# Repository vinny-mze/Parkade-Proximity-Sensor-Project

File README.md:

# microHat Project

Proximity sensor: License and README File

This HAT is a proximity sensor used in Parkade Parking and Home garages
It is used to aid in parking by switching on LED lights if a car gets too close to the wall.

How to use it
Attach sensor to wall
Ensure that all LED lights are in full view of driver's rear mirror
Plug in to 3V-75V DC Source
Keep away from direct sunlight

If car is within 4m from the sensor, 1 LED will switch on this means proceed
If car is within 1.5m from the sensor, 2 LEDs will switch on this means proceed with more caution
if car is less than 0.5m from the wall, all LEDs will switch on this means STOP 

Calvin Induna & Vincent Muzerengwa

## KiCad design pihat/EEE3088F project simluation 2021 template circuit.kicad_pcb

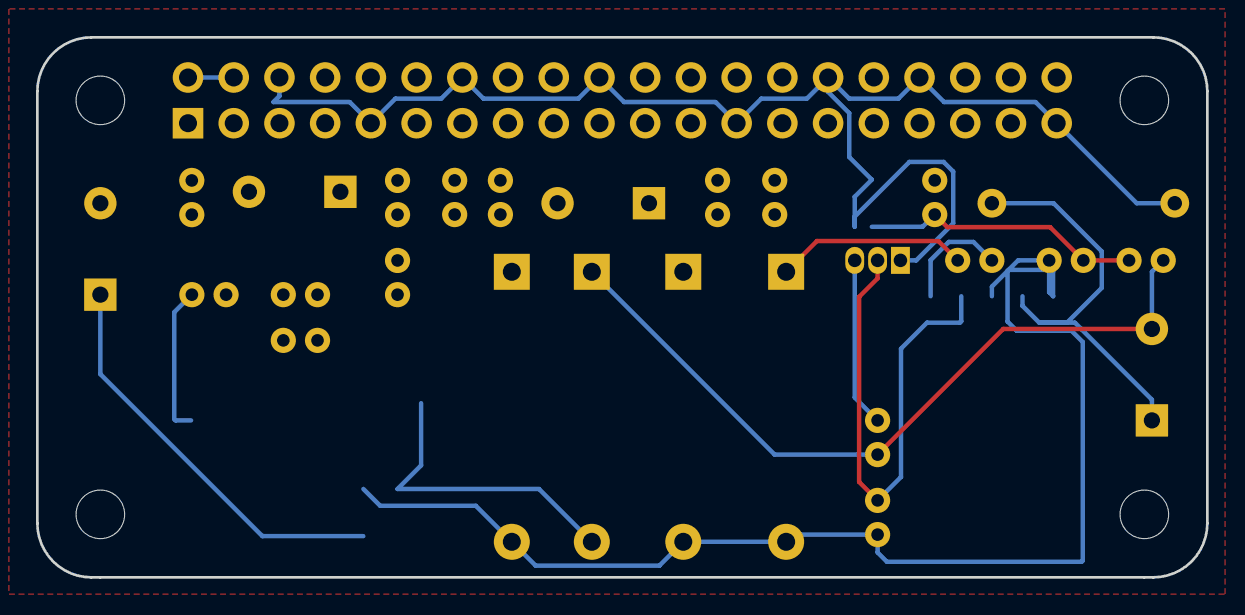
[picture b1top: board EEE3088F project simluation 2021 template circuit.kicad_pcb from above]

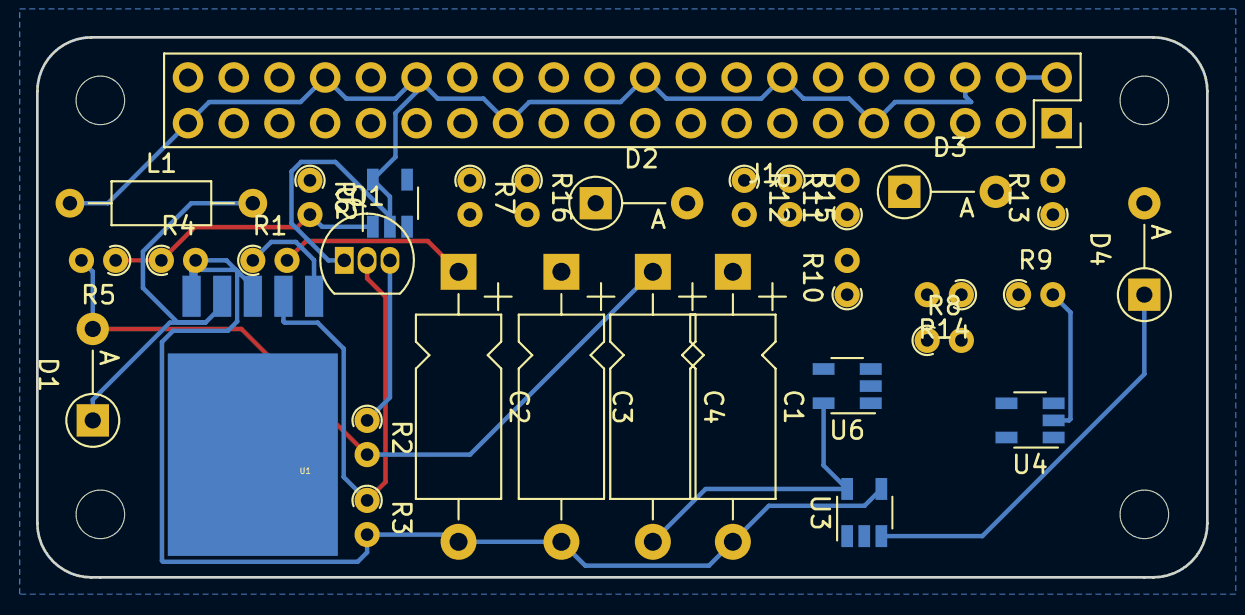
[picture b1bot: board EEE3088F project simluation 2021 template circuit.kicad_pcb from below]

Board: 2 copper layers, 65.0 x 30.0 mm, 36 parts (32 on the bottom side), 24 nets.

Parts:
C1: 33µ; CP_Axial_L10.0mm_D4.5mm_P15.00mm_Horizontal
C2: 0.22µ; CP_Axial_L10.0mm_D4.5mm_P15.00mm_Horizontal
C3: 0.01µ; CP_Axial_L10.0mm_D4.5mm_P15.00mm_Horizontal
C4: 470µ; CP_Axial_L10.0mm_D4.5mm_P15.00mm_Horizontal
D1, D2, D3, D4: D; D_A-405_P5.08mm_Vertical_AnodeUp
H1, H2, H3, H4: MountingHole; MountingHole_2.7mm_M2.5_uHAT_RPi
J1: GPIO_CONNECTOR; PinSocket_2x20_P2.54mm_Vertical_Centered_Anchor
L1: 250µ; L_Axial_L5.3mm_D2.2mm_P10.16mm_Horizontal_Vishay_IM-1
Q1: PNP; TO-92_Inline
R1: 4.7k; R_Axial_DIN0204_L3.6mm_D1.6mm_P1.90mm_Vertical
R2: 2k; R_Axial_DIN0204_L3.6mm_D1.6mm_P1.90mm_Vertical
R3: 1.1k; R_Axial_DIN0204_L3.6mm_D1.6mm_P1.90mm_Vertical
R4, R5, R7: 100; R_Axial_DIN0204_L3.6mm_D1.6mm_P1.90mm_Vertical
R6: 20; R_Axial_DIN0204_L3.6mm_D1.6mm_P1.90mm_Vertical
R8, R9, R10, R11, R12, R13, R14: 1k; R_Axial_DIN0204_L3.6mm_D1.6mm_P1.90mm_Vertical
R15: 300; R_Axial_DIN0204_L3.6mm_D1.6mm_P1.90mm_Vertical
R16: 700; R_Axial_DIN0204_L3.6mm_D1.6mm_P1.90mm_Vertical
U1: LT1082CQPBF; LT1082
U2, U3, U4, U6: OPAMP; TSOT-23-5

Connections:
3.3V: R15.2, R16.1, U2.4, U4.4
5V: C1.2, C2.2, C3.2, J1.2, J1.4, R3.2, R4.2, R8.1, U1.3, U1.5, U3.4
+3V3: J1.1, J1.17, R15.1
/GPIO5: J1.29, R7.1
/GPIO12: J1.32, U3.1, U4.1, U6.1
GND: C1.1, C4.2, J1.6, J1.9, J1.14, J1.20, J1.25, J1.30, J1.34, J1.39, L1.1, Q1.1, R11.2, R12.2, R13.2, R14.2, U2.2, U2.5, U3.5, U4.5, U6.5
unnamed: C2.1, R1.2
unnamed: C3.1, R1.1, U1.1
unnamed: D1.1, L1.2, U1.4
unnamed: D2.1, U6.3
unnamed: D2.2, R12.1
unnamed: D3.1, U4.3
unnamed: D3.2, R13.1
unnamed: D4.1, U3.3
unnamed: D4.2, R14.1
unnamed: Q1.2, R3.1, U1.2
unnamed: Q1.3, R2.1
unnamed: R4.1, R5.1, R6.2, U2.1
unnamed: R6.1, R7.2, U2.3
unnamed: R8.2, R9.1, U3.2
unnamed: R9.2, R10.1, U4.2
unnamed: R10.2, R11.1, U6.2
unnamed: R16.2, U6.4
V(out_spr): C4.1, D1.2, R2.2, R5.2

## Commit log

2021-06-04 Edited readme
2021-06-05 Switching Power Regualtor
2021-06-05 LED Status Circuit
2021-06-05 Amplifier Schematic
2021-06-05 Micro PiHat
2021-06-05 Add LICENSE
2021-06-08 System Requirements and Specifications added
2021-06-08 Simulation files added
2021-06-09 Added 'Opamp Connections Guide'
2021-06-09 Added 'LED Status interpretation'
2021-06-11 Added BOM, Manufacturing notes, reference Material

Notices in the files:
pihat/EEE3088F project simluation 2021 template circuit.kicad_pcb:
This PCB design is licensed under MIT Open Source License.
